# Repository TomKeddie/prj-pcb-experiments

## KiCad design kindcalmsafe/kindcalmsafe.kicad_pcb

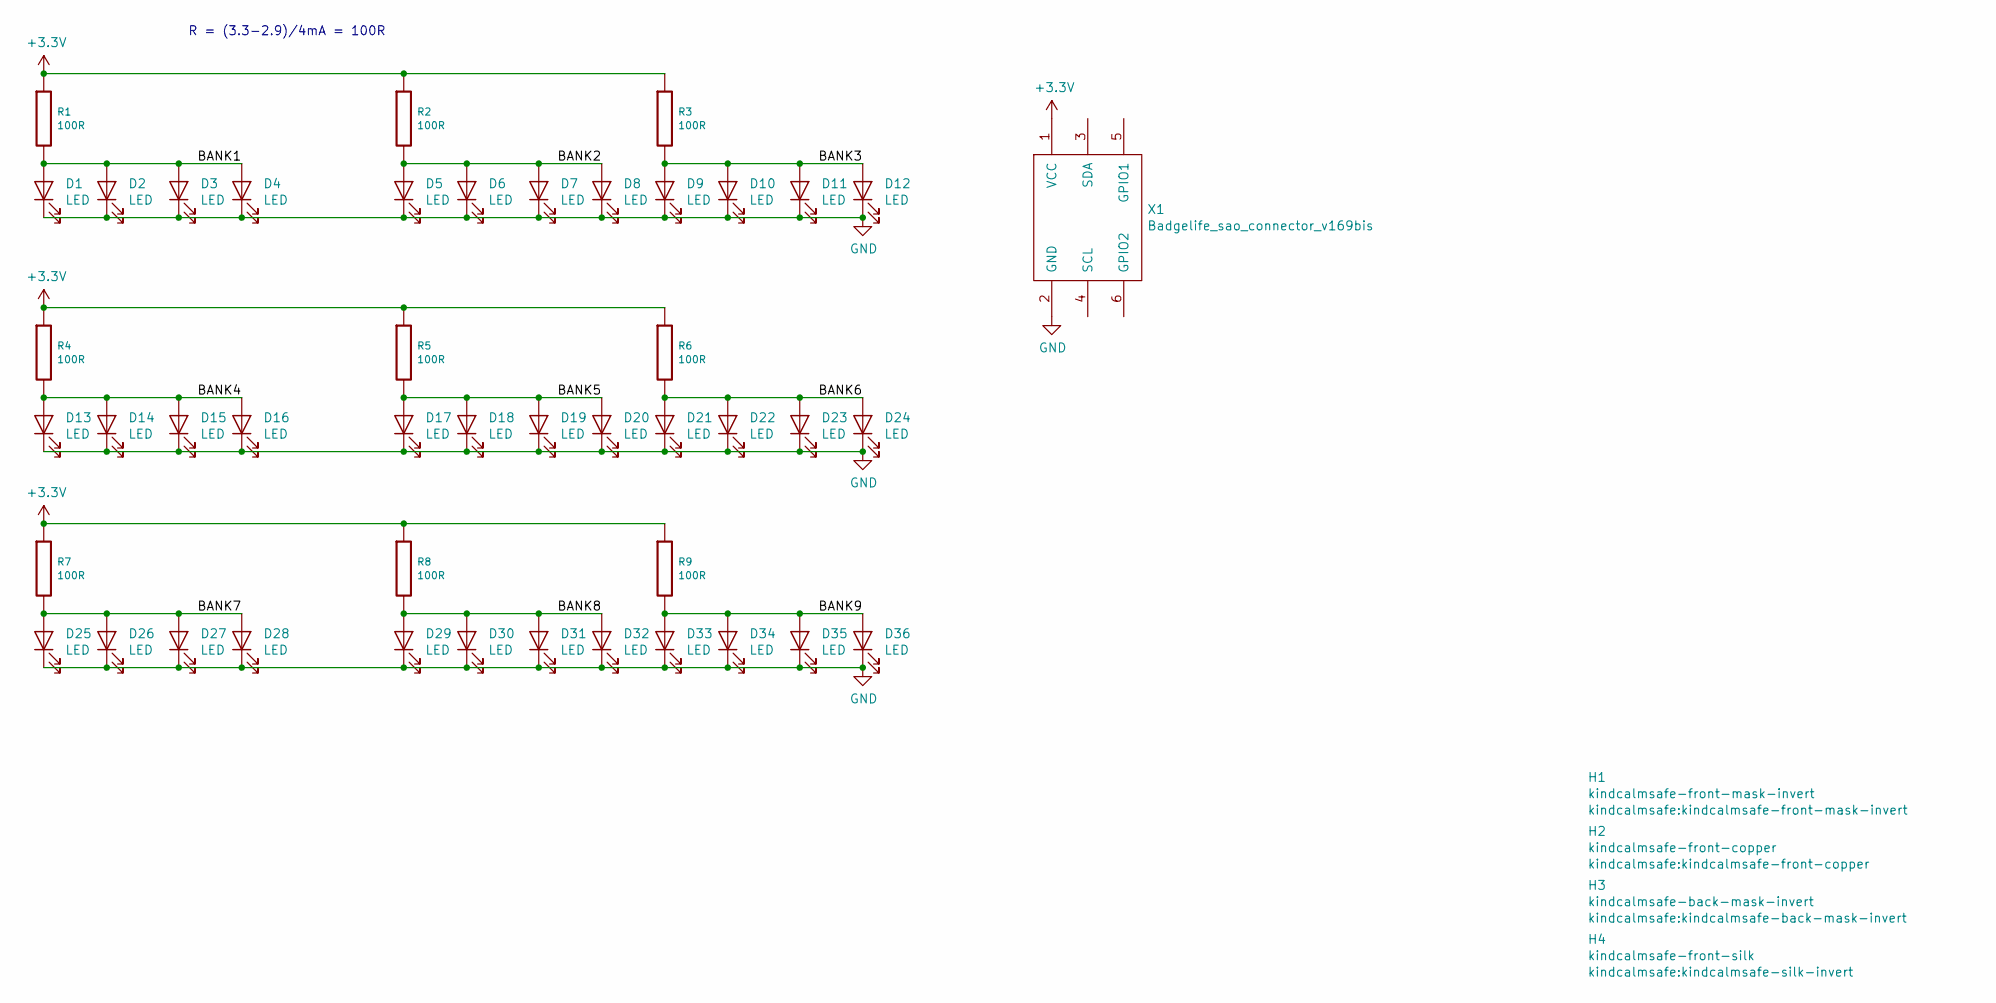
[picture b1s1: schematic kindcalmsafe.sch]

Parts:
D1, D2, D3, D4, D5, D6, D7, D8, D9, D10, D11, D12, D13, D14, D15, D16, D17, D18, D19, D20, D21, D22, D23, D24, D25, D26, D27, D28, D29, D30, D31, D32, D33, D34, D35, D36: LED; ALIEXPRESS_LED_SIDE_1204
H1: kindcalmsafe-front-mask-invert
H2: kindcalmsafe-front-copper
H3: kindcalmsafe-back-mask-invert
H4: kindcalmsafe-front-silk; kindcalmsafe-silk-invert
R1, R2, R3, R4, R5, R6, R7, R8, R9: 100R; R_0805_2012Metric
X1: Badgelife_sao_connector_v169bis; Badgelife-SAOv169-SAO-2x3-SMD-BIGPADS

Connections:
+3V3: R1.1, R2.1, R3.1, R4.1, R5.1, R6.1, R7.1, R8.1, R9.1, X1.1 (VCC)
/BANK1: D1.2 (A), D2.2 (A), D3.2 (A), D4.2 (A), R1.2
/BANK2: D5.2 (A), D6.2 (A), D7.2 (A), D8.2 (A), R2.2
/BANK3: D9.2 (A), D10.2 (A), D11.2 (A), D12.2 (A), R3.2
/BANK4: D13.2 (A), D14.2 (A), D15.2 (A), D16.2 (A), R4.2
/BANK5: D17.2 (A), D18.2 (A), D19.2 (A), D20.2 (A), R5.2
/BANK6: D21.2 (A), D22.2 (A), D23.2 (A), D24.2 (A), R6.2
/BANK7: D25.2 (A), D26.2 (A), D27.2 (A), D28.2 (A), R7.2
/BANK8: D29.2 (A), D30.2 (A), D31.2 (A), D32.2 (A), R8.2
/BANK9: D33.2 (A), D34.2 (A), D35.2 (A), D36.2 (A), R9.2
GND: D1.1 (K), D2.1 (K), D3.1 (K), D4.1 (K), D5.1 (K), D6.1 (K), D7.1 (K), D8.1 (K), D9.1 (K), D10.1 (K), D11.1 (K), D12.1 (K), D13.1 (K), D14.1 (K), D15.1 (K), D16.1 (K), D17.1 (K), D18.1 (K), D19.1 (K), D20.1 (K), D21.1 (K), D22.1 (K), D23.1 (K), D24.1 (K), D25.1 (K), D26.1 (K), D27.1 (K), D28.1 (K), D29.1 (K), D30.1 (K), D31.1 (K), D32.1 (K), D33.1 (K), D34.1 (K), D35.1 (K), D36.1 (K), X1.2 (GND)

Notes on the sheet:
R = (3.3-2.9)/4mA = 100R

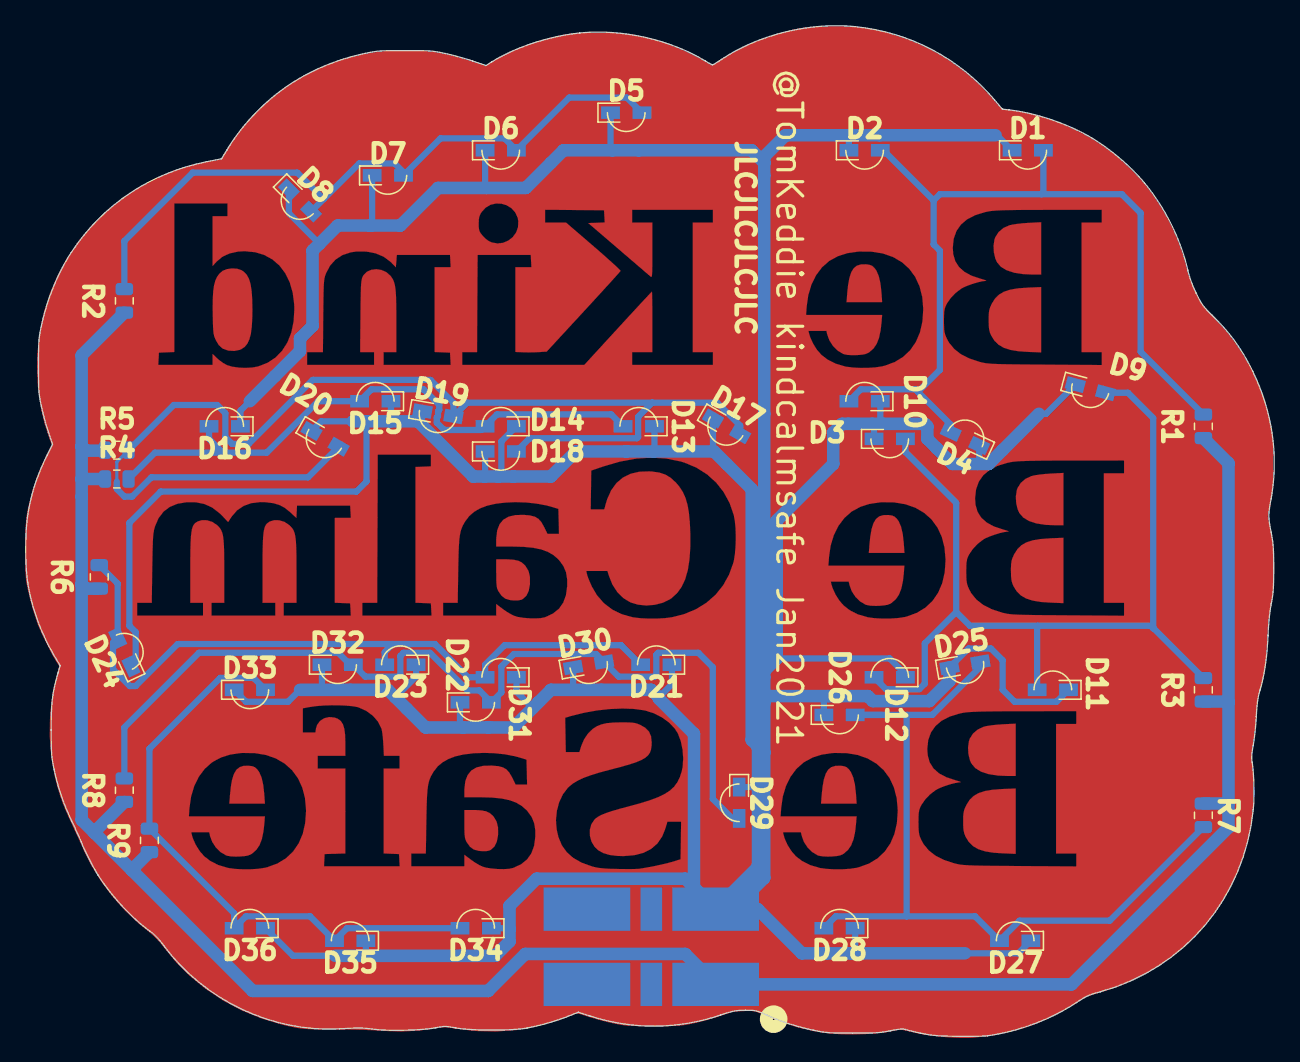
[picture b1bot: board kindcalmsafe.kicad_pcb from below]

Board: 2 copper layers, 99.5 x 80.6 mm, 50 parts (46 on the bottom side), 11 nets.

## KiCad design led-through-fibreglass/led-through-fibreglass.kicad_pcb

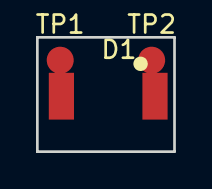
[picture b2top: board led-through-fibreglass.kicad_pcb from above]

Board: 2 copper layers, 7.6 x 6.4 mm, 3 parts (0 on the bottom side), 2 nets.

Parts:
D1: LED; XZM2CYK45WT-9
TP1, TP2: TestPoint; Measurement_Point_Round-SMD-Pad_Small

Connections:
unnamed: D1.1, TP1.1
unnamed: D1.2, TP2.1

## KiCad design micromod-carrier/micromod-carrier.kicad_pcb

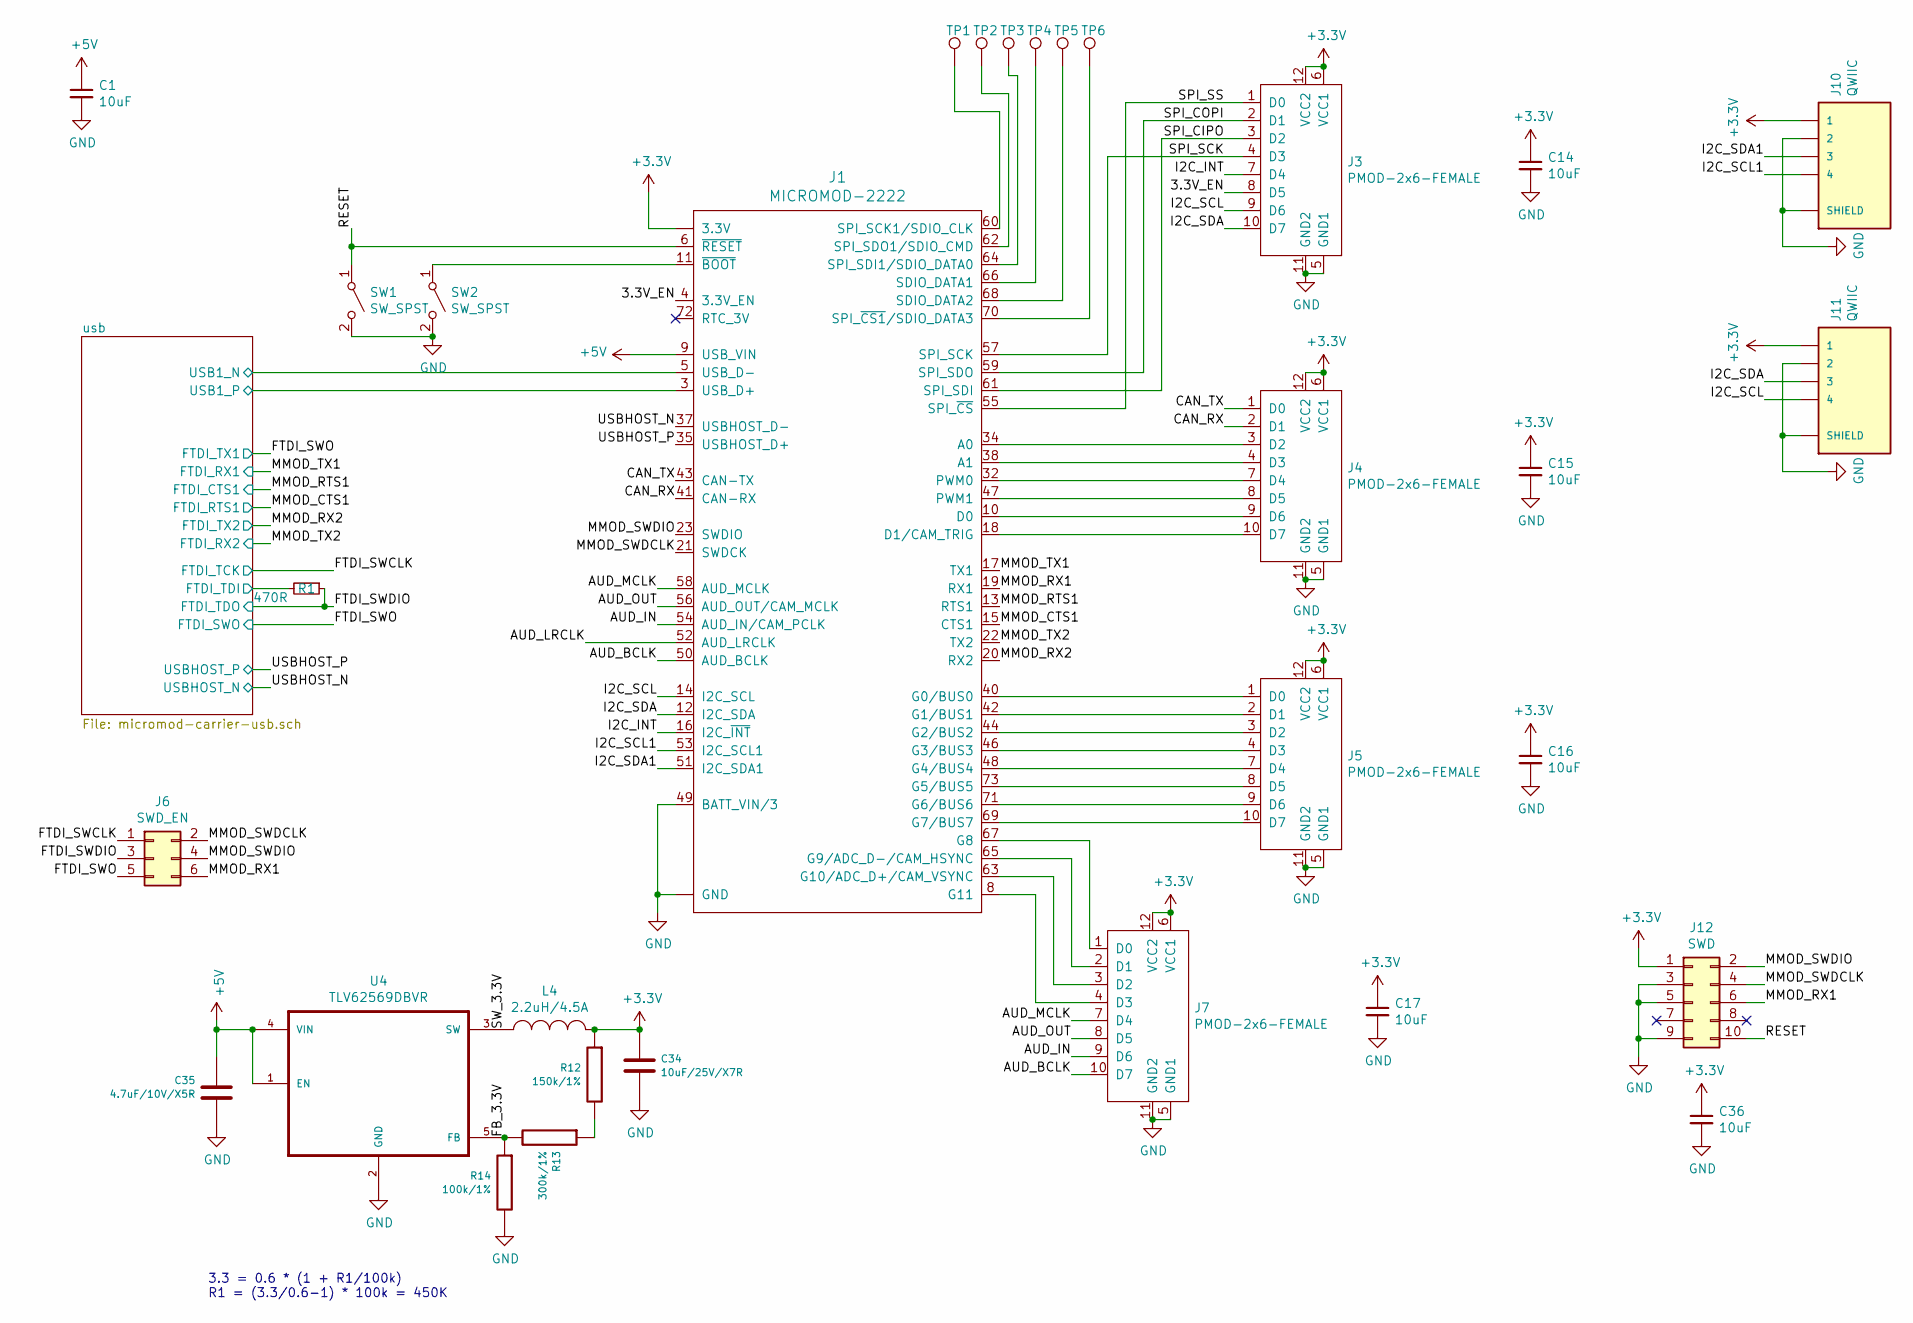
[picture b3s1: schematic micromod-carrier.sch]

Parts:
C1, C14, C15, C16, C17, C36: 10uF; C_0603_1608Metric; LCSC C19702
C34: 10uF/25V/X7R; C_1206_3216Metric; MFGPN C3216X7R1E106M160AE; LCSC C13585
C35: 4.7uF/10V/X5R; C_0402_1005Metric; LCSC C23733
J1: MICROMOD-2222; MDT420E01001
J3, J4, J5, J7: PMOD-2x6-FEMALE; PMOD_2X6_PTH_RA_SOCKET
J6: SWD_EN; PinHeader_2x03_P2.54mm_Vertical
J10, J11: QWIIC; JST_SM04B-SRSS-TB(LF)(SN)
J12: SWD; PinSocket_2x05_P1.27mm_Vertical
L4: 2.2uH/4.5A; L_MWSA0518S; MPN MWSA0518S-2R2MT; LCSC C408345
R1: 470R; R_0603_1608Metric; LCSC C23179
R12: 150k/1%; R_0402_1005Metric; LCSC C25755
R13: 300k/1%; R_0402_1005Metric; LCSC C25774
R14: 100k/1%; R_0402_1005Metric; LCSC C25741
SW1, SW2: SW_SPST; SW_SPST_SMD_2PIN_3.5x6.0
TP1, TP2, TP3, TP4, TP5, TP6: TestPoint; TestPoint_Pad_D1.5mm
U4: TLV62569DBVR; SOT95P280X145-5N; LCSC C141836

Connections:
+3V3: C14.1, C15.1, C16.1, C17.1, C34.2, C36.1, J1.2 (3.3V), J1.74 (3.3V), J3.6 (VCC1), J3.12 (VCC2), J4.6 (VCC1), J4.12 (VCC2), J5.6 (VCC1), J5.12 (VCC2), J7.6 (VCC1), J7.12 (VCC2), J10.1, J11.1, J12.1, L4.2, R12.1; also elsewhere on the board
+5V: C1.1, C35.2, J1.9 (USB_VIN), U4.1 (EN), U4.4 (VIN); also elsewhere on the board
/3.3V_EN: J1.4 (3.3V_EN), J3.8 (D5)
/AUD_BCLK: J1.50 (AUD_BCLK), J7.10 (D7)
/AUD_IN: J1.54 (AUD_IN/CAM_PCLK), J7.9 (D6)
/AUD_LRCLK: J1.52 (AUD_LRCLK)
/AUD_MCLK: J1.58 (AUD_MCLK), J7.7 (D4)
/AUD_OUT: J1.56 (AUD_OUT/CAM_MCLK), J7.8 (D5)
/CAN_RX: J1.41 (CAN-RX), J4.2 (D1)
/CAN_TX: J1.43 (CAN-TX), J4.1 (D0)
/FB_3.3V: R13.2, R14.1, U4.5 (FB)
/FTDI_SWCLK: J6.1; also elsewhere on the board
/FTDI_SWDIO: J6.3, R1.1; also elsewhere on the board
/FTDI_SWO: J6.5; also elsewhere on the board
/I2C_INT: J1.16 (I2C_~INT~), J3.7 (D4)
/I2C_SCL: J1.14 (I2C_SCL), J3.9 (D6), J11.4
/I2C_SCL1: J1.53 (I2C_SCL1), J10.4
/I2C_SDA: J1.12 (I2C_SDA), J3.10 (D7), J11.3
/I2C_SDA1: J1.51 (I2C_SDA1), J10.3
/MMOD_CTS1: J1.15 (CTS1); also elsewhere on the board
/MMOD_RTS1: J1.13 (RTS1); also elsewhere on the board
/MMOD_RX1: J1.19 (RX1), J6.6, J12.6
/MMOD_RX2: J1.20 (RX2); also elsewhere on the board
/MMOD_SWDCLK: J1.21 (SWDCK), J6.2, J12.4
/MMOD_SWDIO: J1.23 (SWDIO), J6.4, J12.2
/MMOD_TX1: J1.17 (TX1); also elsewhere on the board
/MMOD_TX2: J1.22 (TX2); also elsewhere on the board
/RESET: J1.6 (~RESET~), J12.10, SW1.1 (A)
/SPI_CIPO: J1.61 (SPI_SDI), J3.3 (D2)
/SPI_COPI: J1.59 (SPI_SDO), J3.2 (D1)
/SPI_SCK: J1.57 (SPI_SCK), J3.4 (D3)
/SPI_SS: J1.55 (SPI_~CS~), J3.1 (D0)
/SW_3.3V: L4.1, U4.3 (SW)
/USBHOST_N: J1.37 (USBHOST_D-); also elsewhere on the board
/USBHOST_P: J1.35 (USBHOST_D+); also elsewhere on the board
/usb/FTDI_TDI: R1.2; also elsewhere on the board
/usb/USB1_N: J1.5 (USB_D-); also elsewhere on the board
/usb/USB1_P: J1.3 (USB_D+); also elsewhere on the board
GND: C1.2, C14.2, C15.2, C16.2, C17.2, C34.1, C35.1, C36.2, J1.1 (GND), J1.7 (GND), J1.33 (GND), J1.36 (GND), J1.39 (GND), J1.45 (GND), J1.49 (BATT_VIN/3), J1.75 (GND), J1.GND1 (GND), J1.GND2 (GND), J1.GND3 (GND), J3.5 (GND1), J3.11 (GND2), J4.5 (GND1), J4.11 (GND2), J5.5 (GND1), J5.11 (GND2), J7.5 (GND1), J7.11 (GND2), J10.2, J10.S1 (SHIELD), J10.S2 (SHIELD), J11.2, J11.S1 (SHIELD), J11.S2 (SHIELD), J12.3, J12.5, J12.9, R14.2, SW1.2 (B), SW2.2 (B), U4.2 (GND); also elsewhere on the board
unnamed: J1.8 (G11), J7.4 (D3)
unnamed: J1.10 (D0), J4.9 (D6)
unnamed: J1.11 (~BOOT~), SW2.1 (A)
unnamed: J1.18 (D1/CAM_TRIG), J4.10 (D7)
unnamed: J1.32 (PWM0), J4.7 (D4)
unnamed: J1.34 (A0), J4.3 (D2)
unnamed: J1.38 (A1), J4.4 (D3)
unnamed: J1.40 (G0/BUS0), J5.1 (D0)
unnamed: J1.42 (G1/BUS1), J5.2 (D1)
unnamed: J1.44 (G2/BUS2), J5.3 (D2)
unnamed: J1.46 (G3/BUS3), J5.4 (D3)
unnamed: J1.47 (PWM1), J4.8 (D5)
unnamed: J1.48 (G4/BUS4), J5.7 (D4)
unnamed: J1.60 (SPI_SCK1/SDIO_CLK), TP1.1
unnamed: J1.62 (SPI_SDO1/SDIO_CMD), TP2.1
unnamed: J1.63 (G10/ADC_D+/CAM_VSYNC), J7.3 (D2)
unnamed: J1.64 (SPI_SDI1/SDIO_DATA0), TP3.1
unnamed: J1.65 (G9/ADC_D-/CAM_HSYNC), J7.2 (D1)
unnamed: J1.66 (SDIO_DATA1), TP4.1
unnamed: J1.67 (G8), J7.1 (D0)
unnamed: J1.68 (SDIO_DATA2), TP5.1
unnamed: J1.69 (G7/BUS7), J5.10 (D7)
unnamed: J1.70 (SPI_~CS1~/SDIO_DATA3), TP6.1
unnamed: J1.71 (G6/BUS6), J5.9 (D6)
unnamed: J1.73 (G5/BUS5), J5.8 (D5)
unnamed: R12.2, R13.1

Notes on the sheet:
3.3 = 0.6 * (1 + R1/100k) R1 = (3.3/0.6-1) * 100k = 450K

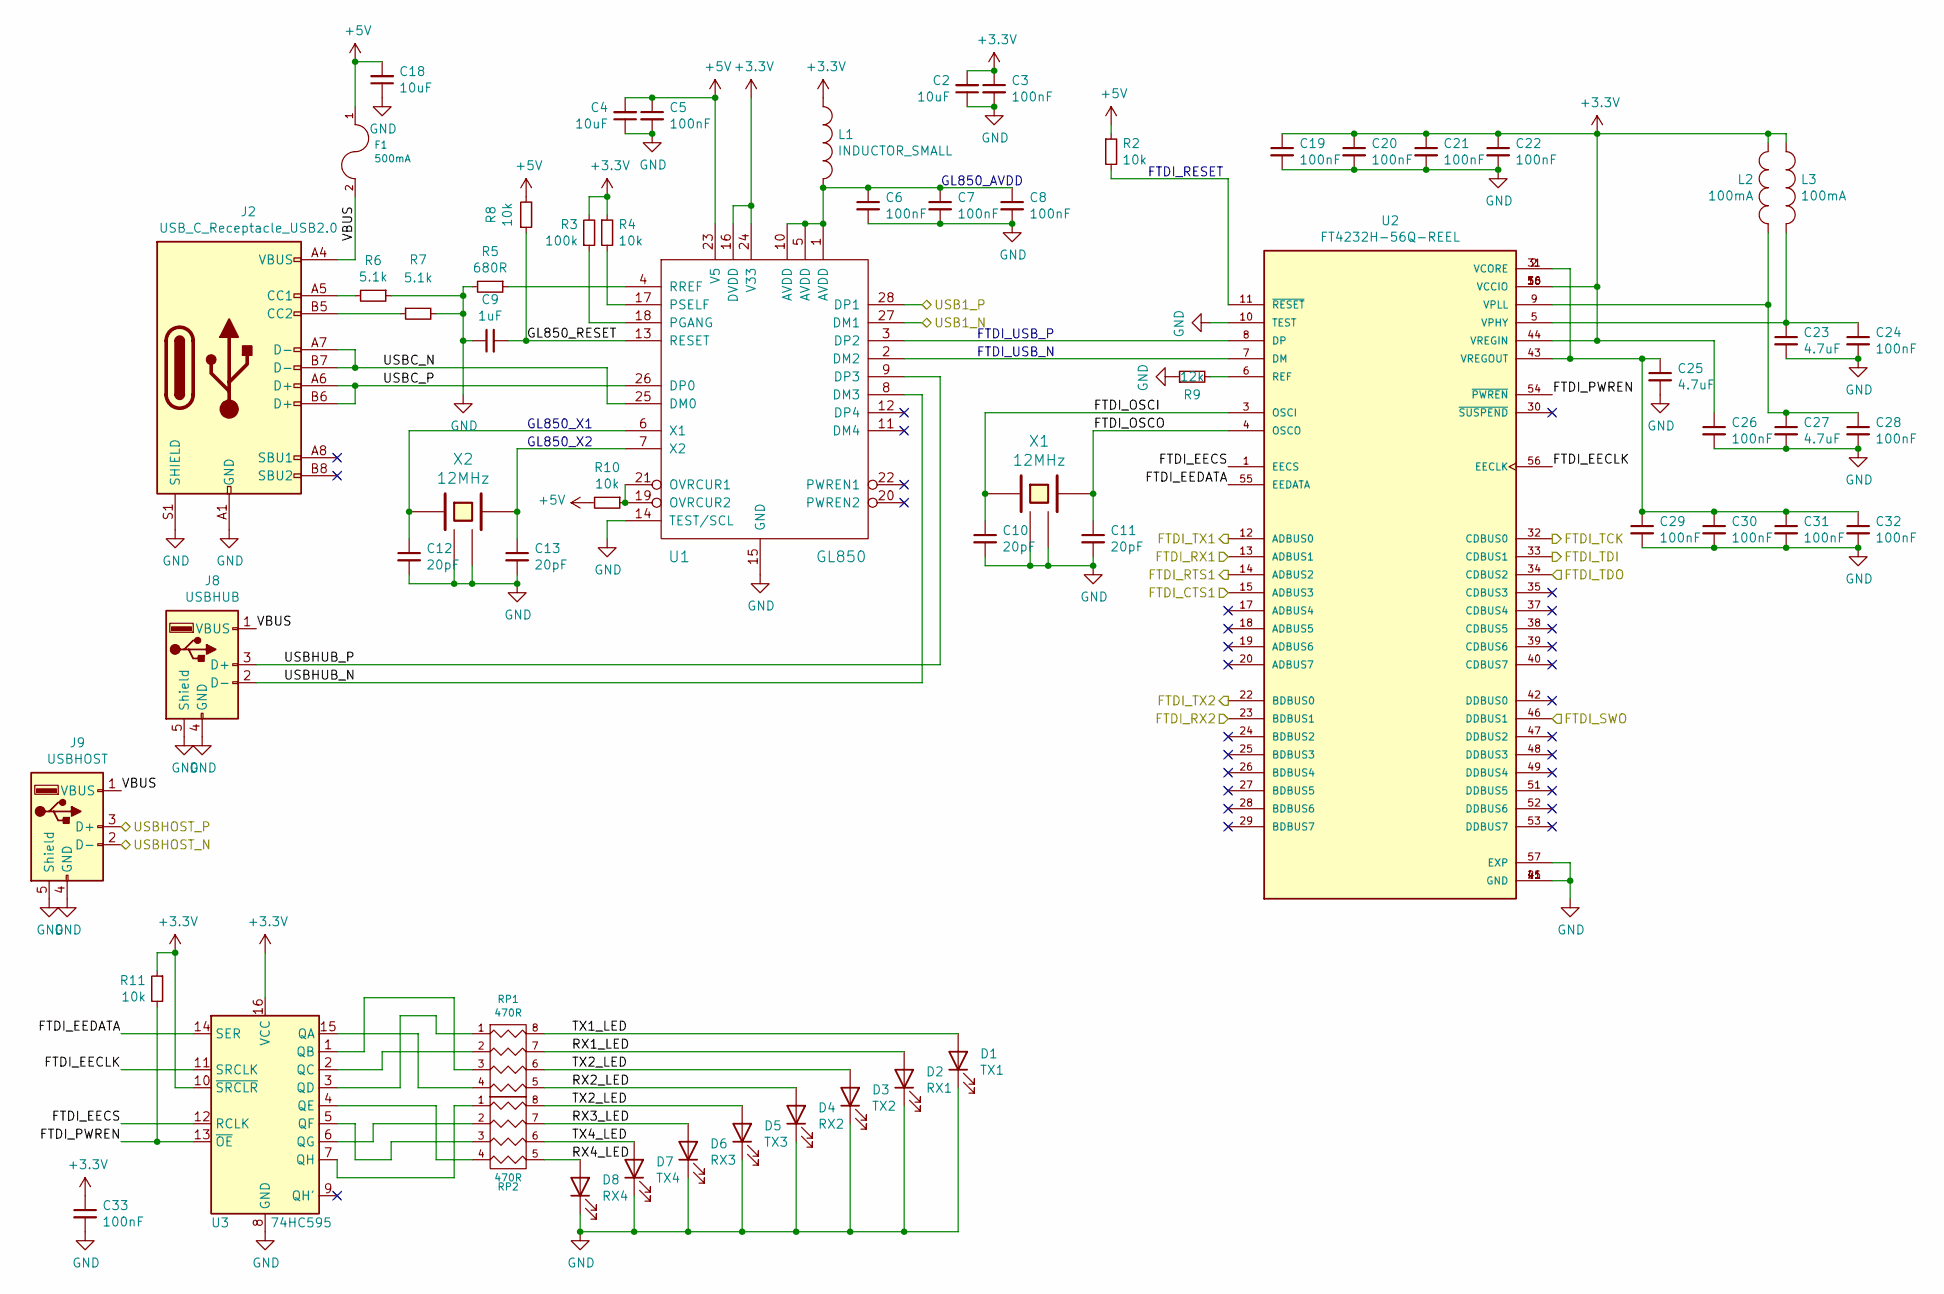
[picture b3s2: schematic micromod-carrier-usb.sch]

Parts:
C2, C4, C18: 10uF; C_0603_1608Metric; LCSC C19702
C3, C5, C6, C7, C8, C19, C20, C21, C22, C24, C26, C28, C29, C30, C31, C32, C33: 100nF; C_0603_1608Metric; LCSC C14663
C9: 1uF; C_0603_1608Metric; LCSC C15849
C10, C11, C12, C13: 20pF; C_0603_1608Metric; LCSC C1648
C23, C25, C27: 4.7uF; C_0603_1608Metric; LCSC C19666
D1: TX1; LED_0603_1608Metric; LCSC C2286
D2: RX1; LED_0603_1608Metric; LCSC C72043
D3: TX2; LED_0603_1608Metric; LCSC C2286
D4: RX2; LED_0603_1608Metric; LCSC C72043
D5: TX3; LED_0603_1608Metric; LCSC C2286
D6: RX3; LED_0603_1608Metric; LCSC C72043
D7: TX4; LED_0603_1608Metric; LCSC C2286
D8: RX4; LED_0603_1608Metric; LCSC C72043
F1: 500mA; C_1206_3216Metric
J2: USB_C_Receptacle_USB2.0; USB_C_Receptacle_GT-USB-7010
J8: USBHUB; OST_USB-A1HSW6
J9: USBHOST; OST_USB-A1HSW6
L1: INDUCTOR_SMALL; C_0805_2012Metric
L2, L3: 100mA; C_0805_2012Metric
R2, R4, R8, R10, R11: 10k; R_0603_1608Metric; LCSC C25804
R3: 100k; R_0603_1608Metric; LCSC C25803
R5: 680R; R_0603_1608Metric; LCSC C23228
R6, R7: 5.1k; R_0603_1608Metric; LCSC C23186
R9: 12k; R_0603_1608Metric; LCSC C22790
RP1, RP2: 470R; R_Array_Convex_4x0603; MPN 4D03WGJ0471T5E; LCSC C25510
U1: GL850; SSOP-28_5.3x10.2mm_P0.65mm; LCSC C136617
U2: FT4232H-56Q-REEL; QFN50P800X800X100-57N
U3: 74HC595; SOIC-16_4.55x10.3mm_P1.27mm
X1, X2: 12MHz; Crystal_SMD_3225-4Pin_3.2x2.5mm; LCSC C9002

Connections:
+3V3: C2.2, C3.1, C19.1, C20.1, C21.1, C22.1, C26.1, C33.1, L1.1, L2.1, L3.1, R3.2, R4.1, R11.1, U1.16 (DVDD), U1.24 (V33), U2.16 (VCCIO), U2.36 (VCCIO), U2.44 (VREGIN), U2.50 (VCCIO), U3.10 (~SRCLR), U3.16 (VCC); also elsewhere on the board
+5V: C4.2, C5.1, C18.2, F1.1, R2.1, R8.2, R10.2, U1.23 (V5); also elsewhere on the board
/FTDI_SWCLK: U2.32 (CDBUS0); also elsewhere on the board
/FTDI_SWDIO: U2.34 (CDBUS2); also elsewhere on the board
/FTDI_SWO: U2.12 (ADBUS0), U2.46 (DDBUS1); also elsewhere on the board
/MMOD_CTS1: U2.14 (ADBUS2); also elsewhere on the board
/MMOD_RTS1: U2.15 (ADBUS3); also elsewhere on the board
/MMOD_RX2: U2.22 (BDBUS0); also elsewhere on the board
/MMOD_TX1: U2.13 (ADBUS1); also elsewhere on the board
/MMOD_TX2: U2.23 (BDBUS1); also elsewhere on the board
/USBHOST_N: J9.2 (D-); also elsewhere on the board
/USBHOST_P: J9.3 (D+); also elsewhere on the board
/usb/FTDI_EECLK: U2.56 (EECLK), U3.11 (SRCLK)
/usb/FTDI_EECS: U2.1 (EECS), U3.12 (RCLK)
/usb/FTDI_EEDATA: U2.55 (EEDATA), U3.14 (SER)
/usb/FTDI_OSCI: C10.1, U2.3 (OSCI), X1.1
/usb/FTDI_OSCO: C11.1, U2.4 (OSCO), X1.3
/usb/FTDI_PWREN: R11.2, U2.54 (~PWREN), U3.13 (~OE)
/usb/FTDI_TDI: U2.33 (CDBUS1); also elsewhere on the board
/usb/GL850_RESET: C9.2, R8.1, U1.13 (RESET)
/usb/RX1_LED: D2.2 (A), RP1.7 (R2)
/usb/RX2_LED: D4.2 (A), RP1.5 (R4)
/usb/RX3_LED: D6.2 (A), RP2.7 (R2)
/usb/RX4_LED: D8.2 (A), RP2.5 (R4)
/usb/TX1_LED: D1.2 (A), RP1.8 (R1)
/usb/TX2_LED: D3.2 (A), D5.2 (A), RP1.6 (R3), RP2.8 (R1)
/usb/TX4_LED: D7.2 (A), RP2.6 (R3)
/usb/USB1_N: U1.27 (DM1); also elsewhere on the board
/usb/USB1_P: U1.28 (DP1); also elsewhere on the board
/usb/USBC_N: J2.A7 (D-), J2.B7 (D-), U1.25 (DM0)
/usb/USBC_P: J2.A6 (D+), J2.B6 (D+), U1.26 (DP0)
/usb/USBHUB_N: J8.2 (D-), U1.8 (DM3)
/usb/USBHUB_P: J8.3 (D+), U1.9 (DP3)
/usb/VBUS: F1.2, J2.A4 (VBUS), J2.A9 (VBUS), J2.B4 (VBUS), J2.B9 (VBUS), J8.1 (VBUS), J9.1 (VBUS)
GND: C2.1, C3.2, C4.1, C5.2, C6.2, C7.2, C8.2, C9.1, C10.2, C11.2, C12.2, C13.2, C18.1, C19.2, C20.2, C21.2, C22.2, C23.2, C24.2, C25.2, C26.2, C27.2, C28.2, C29.2, C30.2, C31.2, C32.2, C33.2, D1.1 (K), D2.1 (K), D3.1 (K), D4.1 (K), D5.1 (K), D6.1 (K), D7.1 (K), D8.1 (K), J2.A1 (GND), J2.A12 (GND), J2.B1 (GND), J2.B12 (GND), J2.S1 (SHIELD), J8.4 (GND), J8.5 (Shield), J9.4 (GND), J9.5 (Shield), R5.2, R6.1, R7.2, R9.1, U1.14 (TEST/SCL), U1.15 (GND), U2.10 (TEST), U2.21 (GND), U2.41 (GND), U2.45 (GND), U2.57 (EXP), U3.8 (GND), X1.2 (GND), X1.4 (GND), X2.2 (GND), X2.4 (GND); also elsewhere on the board
unnamed: C6.1, C7.1, C8.1, L1.2, U1.1 (AVDD), U1.5 (AVDD), U1.10 (AVDD)
unnamed: C12.1, U1.6 (X1), X2.1
unnamed: C13.1, U1.7 (X2), X2.3
unnamed: C23.1, C24.1, L3.2, U2.5 (VPHY)
unnamed: C25.1, C29.1, C30.1, C31.1, C32.1, U2.2 (VCORE), U2.31 (VCORE), U2.43 (VREGOUT)
unnamed: C27.1, C28.1, L2.2, U2.9 (VPLL)
unnamed: J2.A5 (CC1), R6.2
unnamed: J2.B5 (CC2), R7.1
unnamed: R2.2, U2.11 (~RESET)
unnamed: R3.1, U1.18 (PGANG)
unnamed: R4.2, U1.17 (PSELF)
unnamed: R5.1, U1.4 (RREF)
unnamed: R9.2, U2.6 (REF)
unnamed: R10.1, U1.19 (OVRCUR2), U1.21 (OVRCUR1)
unnamed: RP1.1, U3.3 (QD)
unnamed: RP1.2, U3.2 (QC)
unnamed: RP1.3, U3.1 (QB)
unnamed: RP1.4, U3.15 (QA)
unnamed: RP2.1, U3.7 (QH)
unnamed: RP2.2, U3.6 (QG)
unnamed: RP2.3, U3.5 (QF)
unnamed: RP2.4, U3.4 (QE)
unnamed: U1.2 (DM2), U2.7 (DM)
unnamed: U1.3 (DP2), U2.8 (DP)

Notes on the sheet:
FTDI_RESET
GL850_AVDD
FTDI_USB_P
FTDI_USB_N
GL850_X1
GL850_X2

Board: 2 copper layers, 91 parts (0 on the bottom side), 107 nets, no tracks yet.

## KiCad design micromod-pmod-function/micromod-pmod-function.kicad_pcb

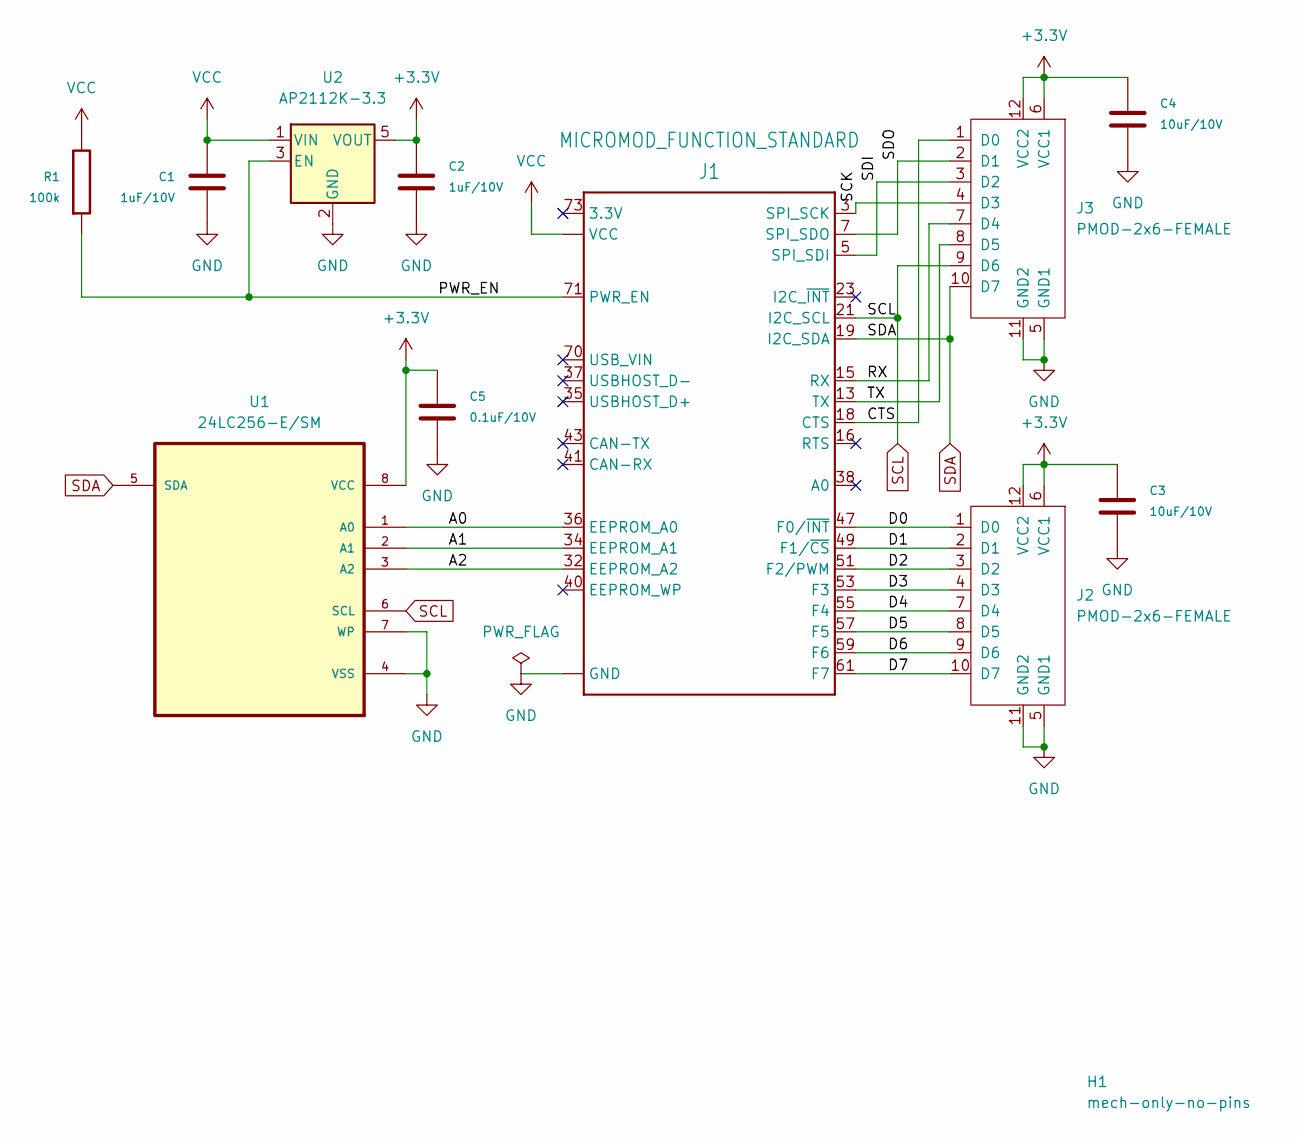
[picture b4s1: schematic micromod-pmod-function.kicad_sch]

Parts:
C1, C2: 1uF/10V; C_0805_2012Metric_Pad1.15x1.40mm_HandSolder; LCSC DNP
C3, C4: 10uF/10V; C_0805_2012Metric_Pad1.15x1.40mm_HandSolder; LCSC DNP
C5: 0.1uF/10V; C_0805_2012Metric_Pad1.15x1.40mm_HandSolder; LCSC DNP
H1: mech-only-no-pins; mask
J1: MICROMOD_FUNCTION_STANDARD
J2, J3: PMOD-2x6-FEMALE; PMOD_2X6_PTH_RA_SOCKET
R1: 100k; R_0805_2012Metric; LCSC DNP
U1: 24LC256-E/SM; SOIC127P600X175-8N; MPN 24LC256-E/SM
U2: AP2112K-3.3; SOT-23-5

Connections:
+3V3: C2.1, C3.1, C4.1, C5.1, J2.6 (VCC1), J2.12 (VCC2), J3.6 (VCC1), J3.12 (VCC2), U1.8 (VCC), U2.5 (VOUT)
/A0: J1.36 (EEPROM_A0), U1.1 (A0)
/A1: J1.34 (EEPROM_A1), U1.2 (A1)
/A2: J1.32 (EEPROM_A2), U1.3 (A2)
/CTS: J1.18 (CTS), J3.1 (D0)
/D0: J1.47 (F0/~INT), J2.1 (D0)
/D1: J1.49 (F1/~CS), J2.2 (D1)
/D2: J1.51 (F2/PWM), J2.3 (D2)
/D3: J1.53 (F3), J2.4 (D3)
/D4: J1.55 (F4), J2.7 (D4)
/D5: J1.57 (F5), J2.8 (D5)
/D6: J1.59 (F6), J2.9 (D6)
/D7: J1.61 (F7), J2.10 (D7)
/PWR_EN: J1.71 (PWR_EN), R1.1, U2.3 (EN)
/RX: J1.15 (RX), J3.7 (D4)
/SCK: J1.3 (SPI_SCK), J3.4 (D3)
/SDI: J1.5 (SPI_SDI), J3.3 (D2)
/SDO: J1.7 (SPI_SDO), J3.2 (D1)
/TX: J1.13 (TX), J3.8 (D5)
GND: C1.1, C2.2, C3.2, C4.2, C5.2, J1.1 (GND), J1.33 (GND), J1.39 (GND), J1.45 (GND), J1.75 (GND), J2.5 (GND1), J2.11 (GND2), J3.5 (GND1), J3.11 (GND2), U1.4 (VSS), U1.7 (WP), U2.2 (GND)
SCL: J1.21 (I2C_SCL), J3.9 (D6), U1.6 (SCL)
SDA: J1.19 (I2C_SDA), J3.10 (D7), U1.5 (SDA)
VCC: C1.2, J1.72 (VCC), J1.74 (VCC), R1.2, U2.1 (VIN)

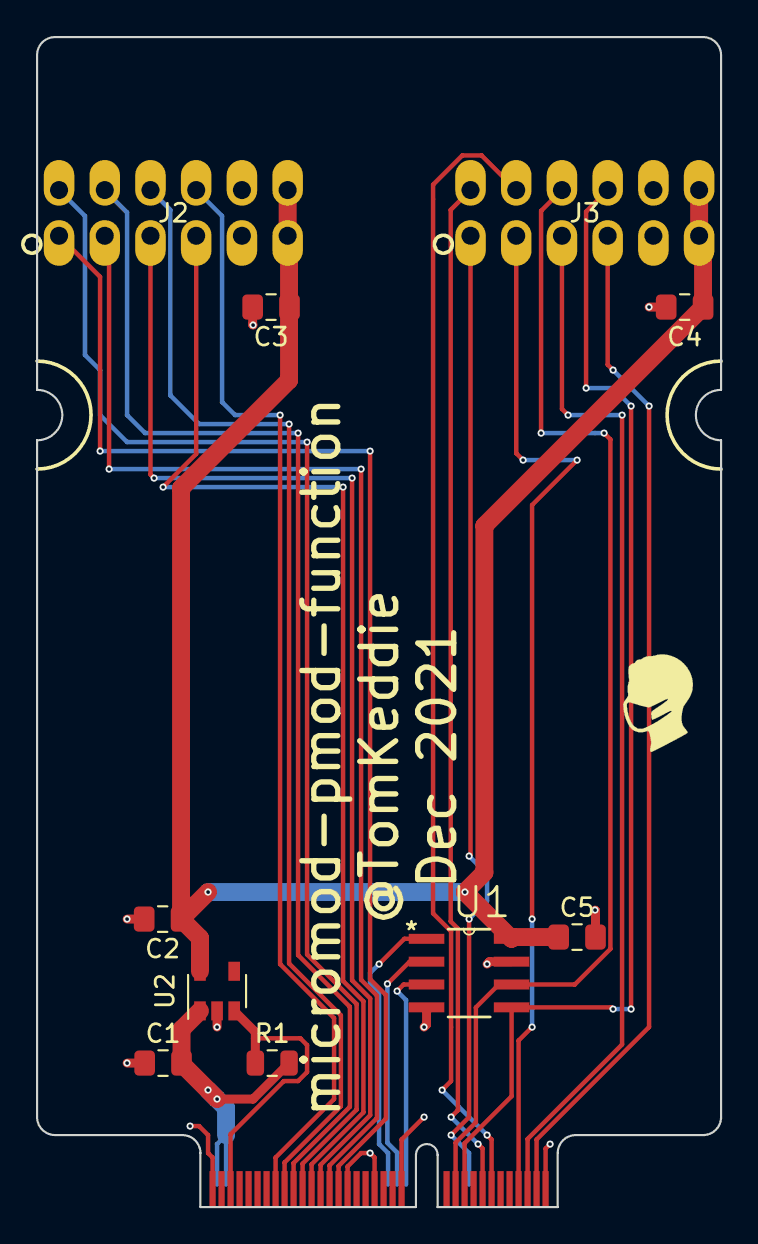
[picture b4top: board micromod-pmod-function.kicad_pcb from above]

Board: 2 copper layers, 38.0 x 65.0 mm, 12 parts (0 on the bottom side), 23 nets.

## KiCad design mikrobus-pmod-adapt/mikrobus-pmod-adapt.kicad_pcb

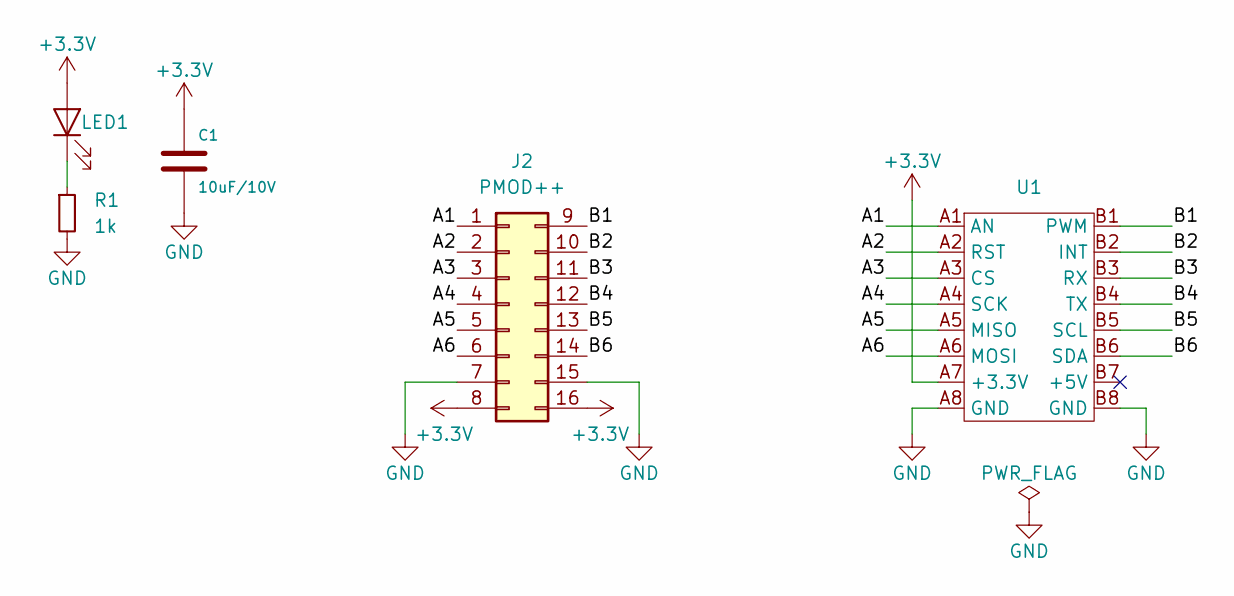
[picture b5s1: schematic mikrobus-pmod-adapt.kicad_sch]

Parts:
C1: 10uF/10V; C_1206_3216Metric_Pad1.42x1.75mm_HandSolder; LCSC DNP
J2: PMOD++; PMOD_2x8_PTH_RA_SOCKET
LED1: LED; LED_1206_3216Metric
R1: 1k; R_1206_3216Metric; MFGPN 0402WGF1001TCE; LCSC C11702
U1: MIKROBUS_ADD_ON_SMALL

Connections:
+3.3V: C1.1, J2.8, J2.16, LED1.2 (A), U1.A7 (+3.3V)
/A1: J2.1, U1.A1 (AN)
/A2: J2.2, U1.A2 (RST)
/A3: J2.3, U1.A3 (CS)
/A4: J2.4, U1.A4 (SCK)
/A5: J2.5, U1.A5 (MISO)
/A6: J2.6, U1.A6 (MOSI)
/B1: J2.9, U1.B1 (PWM)
/B2: J2.10, U1.B2 (INT)
/B3: J2.11, U1.B3 (RX)
/B4: J2.12, U1.B4 (TX)
/B5: J2.13, U1.B5 (SCL)
/B6: J2.14, U1.B6 (SDA)
GND: C1.2, J2.7, J2.15, R1.2, U1.A8 (GND), U1.B8 (GND)
unnamed: LED1.1 (K), R1.1

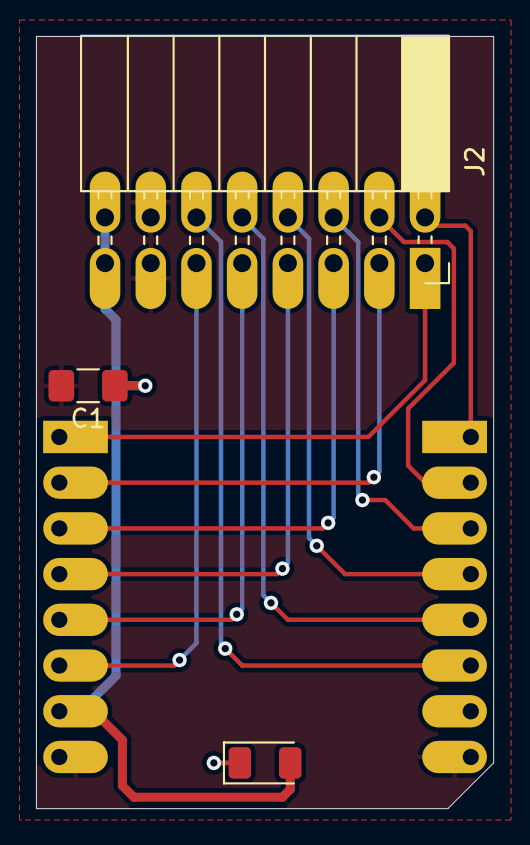
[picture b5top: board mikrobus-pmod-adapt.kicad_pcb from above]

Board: 2 copper layers, 25.4 x 42.9 mm, 5 parts (1 on the bottom side), 15 nets.

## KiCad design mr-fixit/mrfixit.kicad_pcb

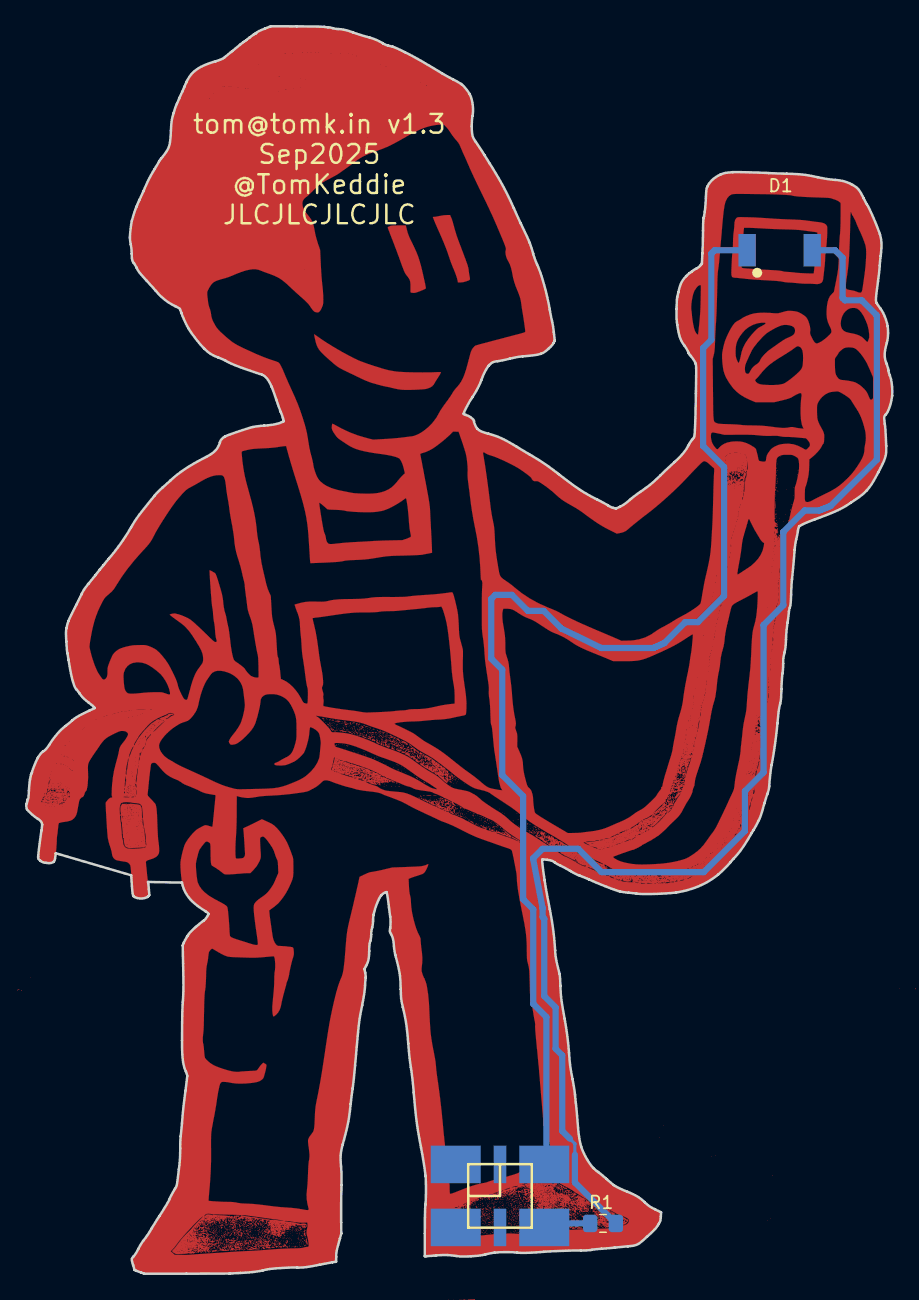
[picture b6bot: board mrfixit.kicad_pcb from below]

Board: 2 copper layers, 69.3 x 99.8 mm, 5 parts (3 on the bottom side), 3 nets.

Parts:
D1: LED; XZM2CYK45WT-9-NOMASK
H1: Solder Mask; mrfixit-mask
H2: Copper; mrfixit-copper
J1: Conn_02x03_Odd_Even; PinSocket_2x03_P2.54mm_Vertical_SMD_SAO
R1: 220R; C_0805_2012Metric_Pad1.15x1.40mm_HandSolder

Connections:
+3V3: D1.2, J1.5
GND: J1.6, R1.2
unnamed: D1.1, R1.1

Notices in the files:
parts and their libraries:
Copyright 2016 Accelerated Designs. All rights reserved.
